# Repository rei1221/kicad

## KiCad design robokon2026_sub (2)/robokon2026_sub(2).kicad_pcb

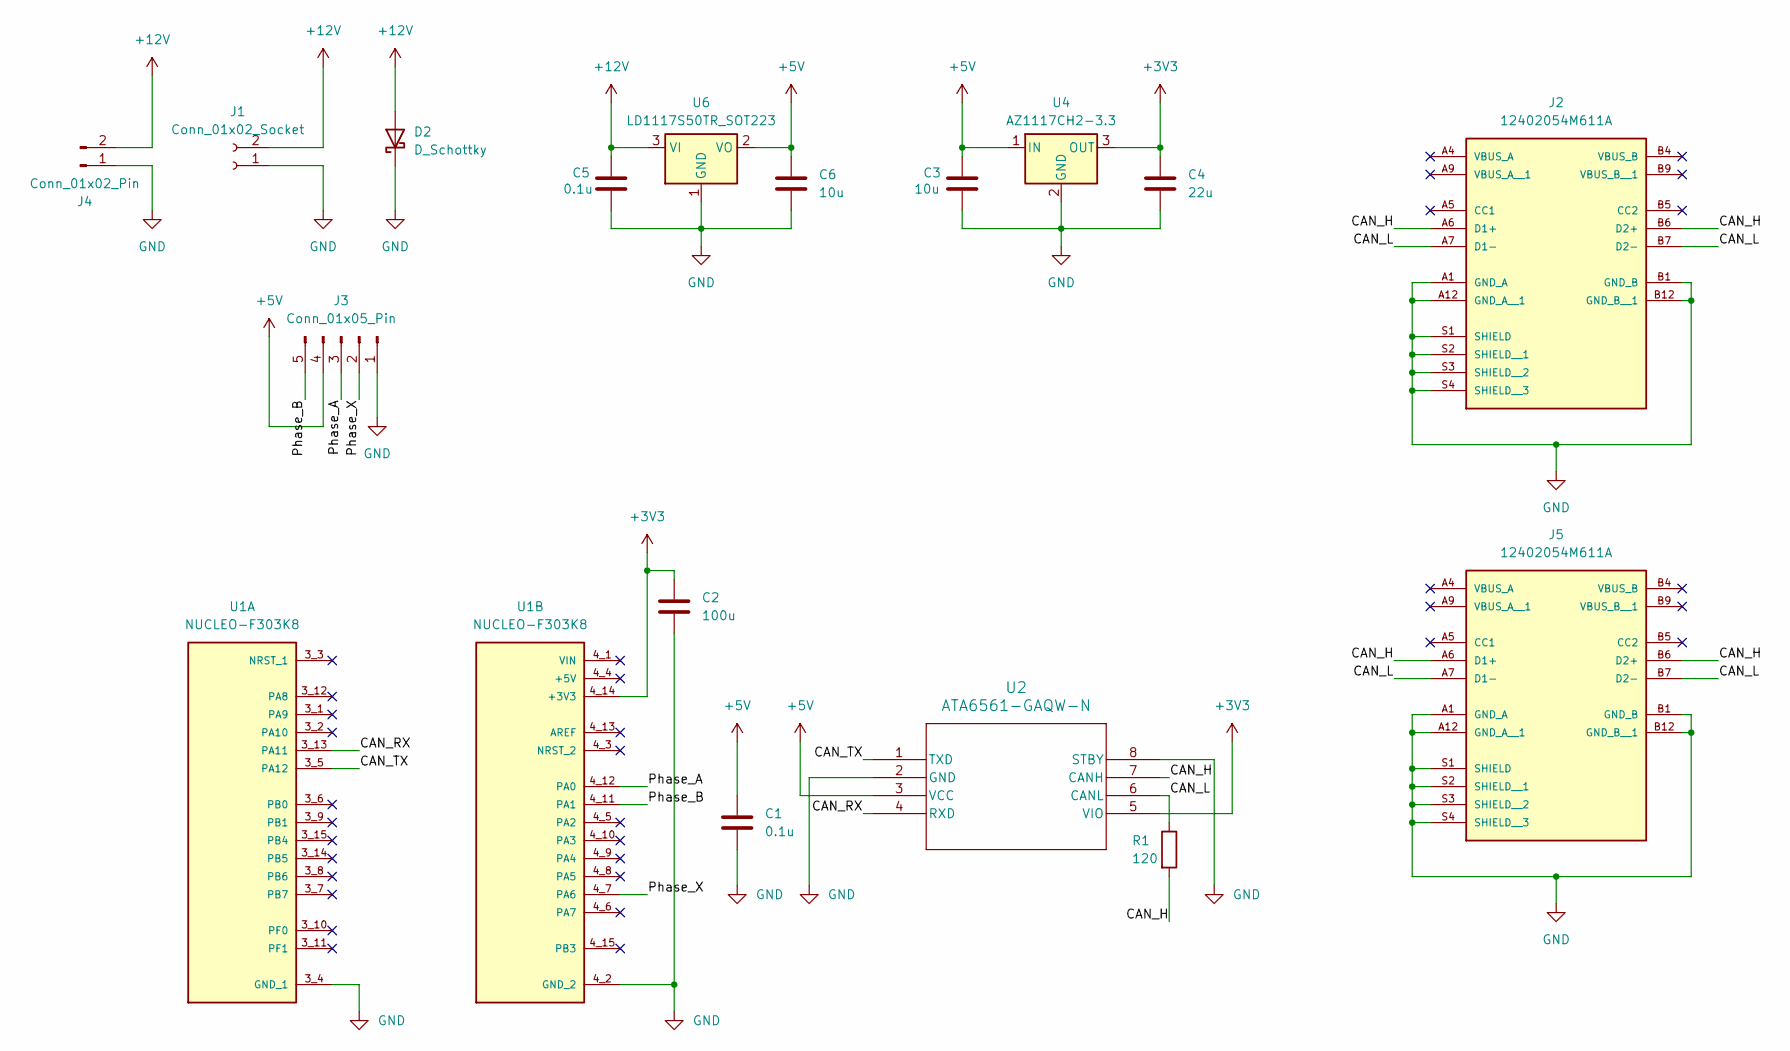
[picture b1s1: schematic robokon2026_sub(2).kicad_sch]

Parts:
C1, C5: 0.1u; C_0805_2012Metric_Pad1.18x1.45mm_HandSolder
C2: 100u; CP_Radial_D10.0mm_P5.00mm
C3, C6: 10u; C_0805_2012Metric_Pad1.18x1.45mm_HandSolder
C4: 22u; C_0805_2012Metric_Pad1.18x1.45mm_HandSolder
D2: D_Schottky; D_SMC
J1: Conn_01x02_Socket; AMASS_XT30PW-F_1x02_P2.50mm_Horizontal
J2, J5: 12402054M611A; AMPHENOL_12402054M611A; PARTREV 3
J3: Conn_01x05_Pin; JST_XH_S5B-XH-A_1x05_P2.50mm_Horizontal
J4: Conn_01x02_Pin; AMASS_XT30PW-M_1x02_P2.50mm_Horizontal
R1: 120; R_0603_1608Metric_Pad0.98x0.95mm_HandSolder
U1: NUCLEO-F303K8; MODULE_NUCLEO-F303K8; PARTREV 5; DigiKey_Part_Number 497-15981-ND
U2: ATA6561-GAQW-N; SOIC8_4P9X3P9MC_MCH
U4: AZ1117CH2-3.3; SOT-223-3_TabPin2
U6: LD1117S50TR_SOT223; SOT-223-3_TabPin2

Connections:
+3V3: C2.1, C4.1, U1.4_14 (+3V3), U2.5 (VIO), U4.3 (OUT)
+5V: C1.1, C3.1, C6.1, J3.4, U2.3 (VCC), U4.1 (IN), U6.2 (VO)
+12V: C5.1, D2.2 (A), J1.2, J4.2, U6.3 (VI)
/CAN_H: J2.A6 (D1+), J2.B6 (D2+), J5.A6 (D1+), J5.B6 (D2+), R1.2, U2.7 (CANH)
/CAN_L: J2.A7 (D1-), J2.B7 (D2-), J5.A7 (D1-), J5.B7 (D2-), R1.1, U2.6 (CANL)
/CAN_RX: U1.3_13 (PA11), U2.4 (RXD)
/CAN_TX: U1.3_5 (PA12), U2.1 (TXD)
/Phase_A: J3.3, U1.4_12 (PA0)
/Phase_B: J3.5, U1.4_11 (PA1)
/Phase_X: J3.2, U1.4_7 (PA6)
GND: C1.2, C2.2, C3.2, C4.2, C5.2, C6.2, D2.1 (K), J1.1, J2.A1 (GND_A), J2.A12 (GND_A__1), J2.B1 (GND_B), J2.B12 (GND_B__1), J2.S1 (SHIELD), J2.S2 (SHIELD__1), J2.S3 (SHIELD__2), J2.S4 (SHIELD__3), J3.1, J4.1, J5.A1 (GND_A), J5.A12 (GND_A__1), J5.B1 (GND_B), J5.B12 (GND_B__1), J5.S1 (SHIELD), J5.S2 (SHIELD__1), J5.S3 (SHIELD__2), J5.S4 (SHIELD__3), U1.3_4 (GND_1), U1.4_2 (GND_2), U2.2 (GND), U2.8 (STBY), U4.2 (GND), U6.1 (GND)

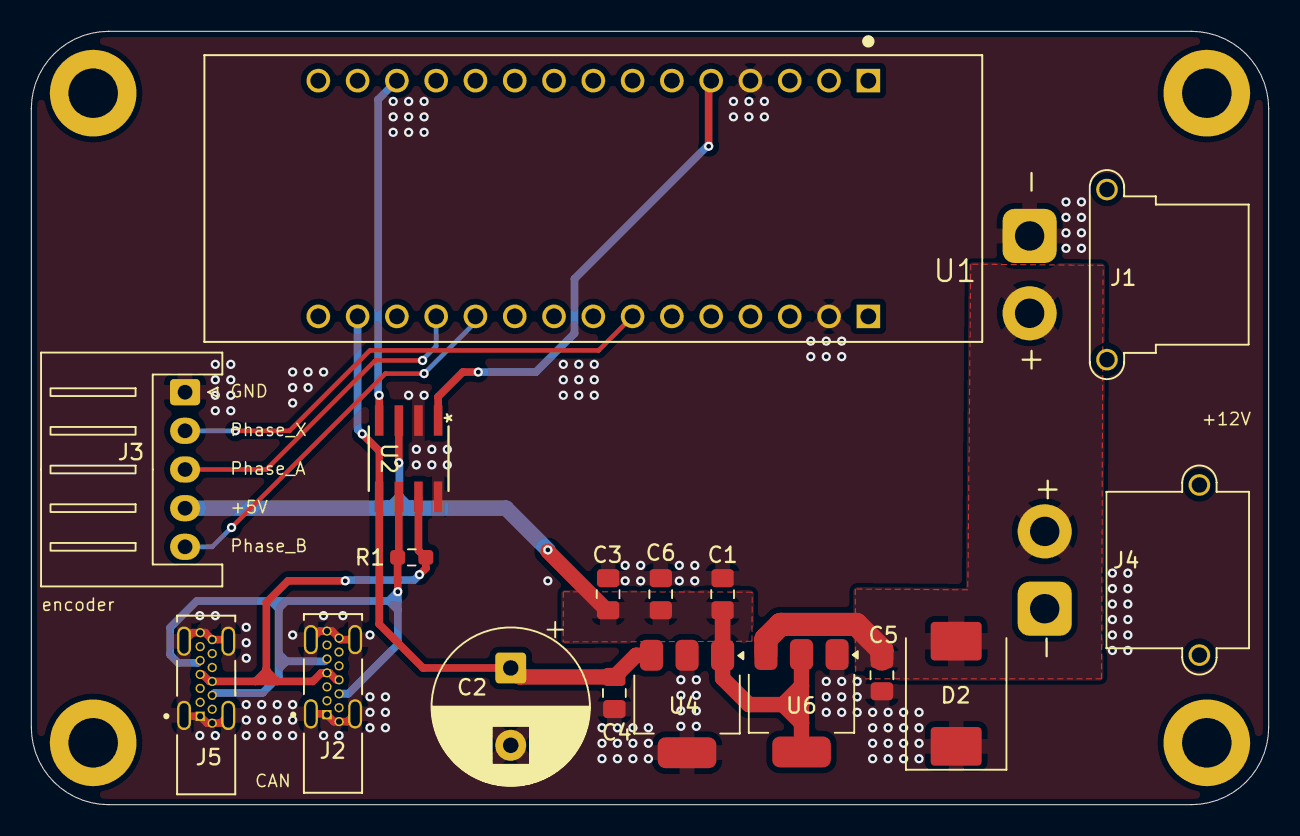
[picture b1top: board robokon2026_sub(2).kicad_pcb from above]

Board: 2 copper layers, 80.0 x 50.0 mm, 17 parts (0 on the bottom side), 11 nets.

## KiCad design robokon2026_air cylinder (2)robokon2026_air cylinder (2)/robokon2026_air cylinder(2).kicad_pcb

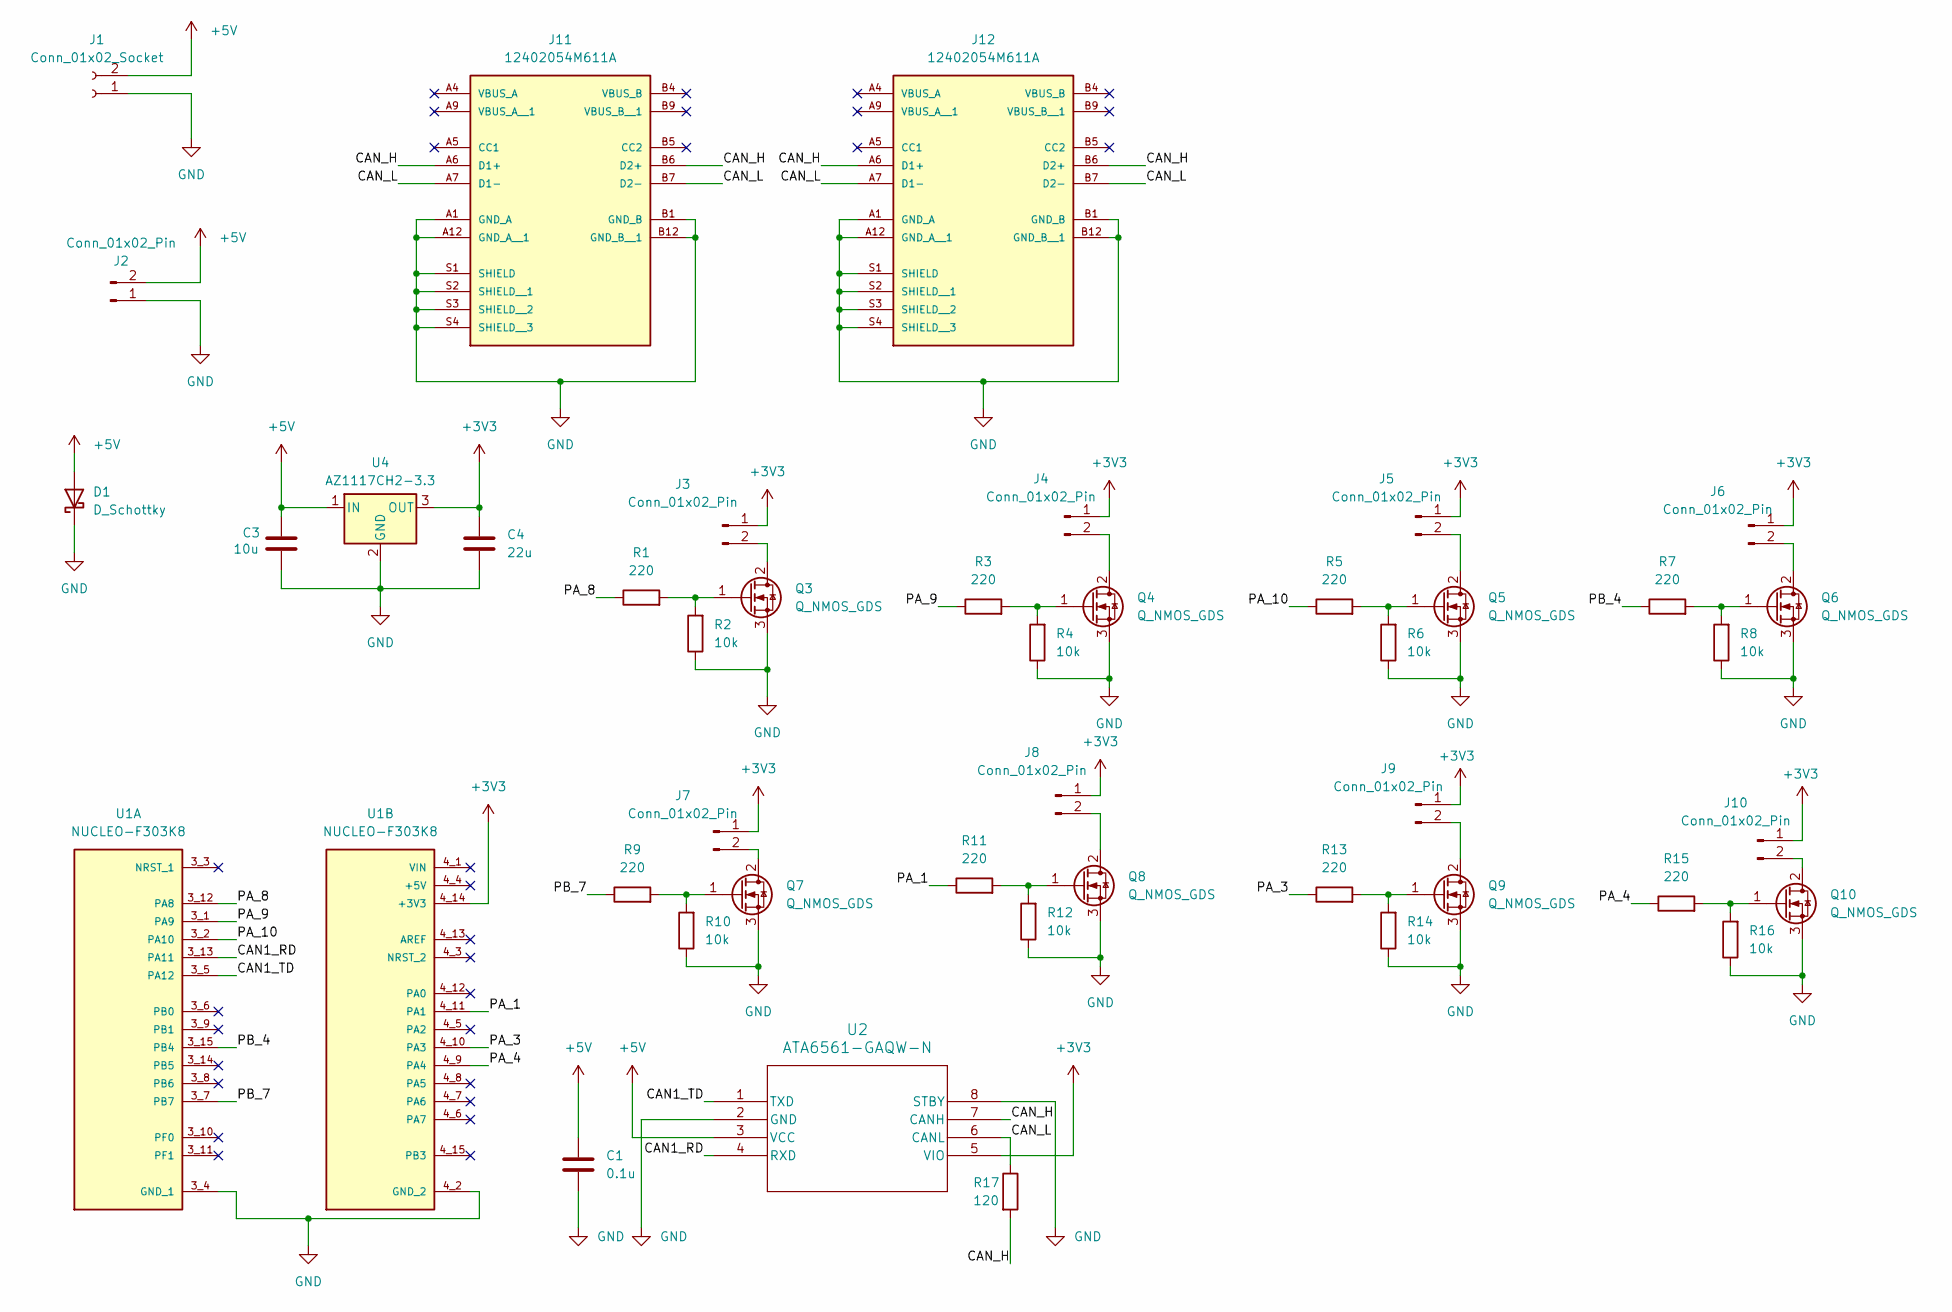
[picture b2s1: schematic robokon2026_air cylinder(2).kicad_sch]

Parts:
C1: 0.1u; C_0805_2012Metric_Pad1.18x1.45mm_HandSolder
C3: 10u; C_0805_2012Metric_Pad1.18x1.45mm_HandSolder
C4: 22u; C_0805_2012Metric_Pad1.18x1.45mm_HandSolder
D1: D_Schottky; D_SMC
J1: Conn_01x02_Socket; AMASS_XT30PW-F_1x02_P2.50mm_Horizontal
J2: Conn_01x02_Pin; AMASS_XT30PW-M_1x02_P2.50mm_Horizontal
J3, J4, J5, J6, J7, J8, J9, J10: Conn_01x02_Pin; CONN_B02B-PASKLFSN_JST
J11, J12: 12402054M611A; AMPHENOL_12402054M611A; PARTREV 3
Q3, Q4, Q5, Q6, Q7, Q8, Q9, Q10: Q_NMOS_GDS; TO-252-3_TabPin2
R1, R3, R5, R7, R9, R11, R13, R15: 220; R_0603_1608Metric_Pad0.98x0.95mm_HandSolder
R2, R4, R6, R8, R10, R12, R14, R16: 10k; R_0603_1608Metric_Pad0.98x0.95mm_HandSolder
R17: 120; R_0603_1608Metric_Pad0.98x0.95mm_HandSolder
U1: NUCLEO-F303K8; MODULE_NUCLEO-F303K8; PARTREV 5; DigiKey_Part_Number 497-15981-ND
U2: ATA6561-GAQW-N; SOIC8_4P9X3P9MC_MCH
U4: AZ1117CH2-3.3; SOT-223-3_TabPin2

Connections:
+3V3: C4.1, J3.1, J4.1, J5.1, J6.1, J7.1, J8.1, J9.1, J10.1, U1.4_14 (+3V3), U2.5 (VIO), U4.3 (OUT)
+5V: C1.1, C3.1, D1.2 (A), J1.2, J2.2, U2.3 (VCC), U4.1 (IN)
/CAN1_RD: U1.3_13 (PA11), U2.4 (RXD)
/CAN1_TD: U1.3_5 (PA12), U2.1 (TXD)
/CAN_H: J11.A6 (D1+), J11.B6 (D2+), J12.A6 (D1+), J12.B6 (D2+), R17.2, U2.7 (CANH)
/CAN_L: J11.A7 (D1-), J11.B7 (D2-), J12.A7 (D1-), J12.B7 (D2-), R17.1, U2.6 (CANL)
/PA_1: R11.1, U1.4_11 (PA1)
/PA_3: R13.1, U1.4_10 (PA3)
/PA_4: R15.1, U1.4_9 (PA4)
/PA_8: R1.1, U1.3_12 (PA8)
/PA_9: R3.1, U1.3_1 (PA9)
/PA_10: R5.1, U1.3_2 (PA10)
/PB_4: R7.1, U1.3_15 (PB4)
/PB_7: R9.1, U1.3_7 (PB7)
GND: C1.2, C3.2, C4.2, D1.1 (K), J1.1, J2.1, J11.A1 (GND_A), J11.A12 (GND_A__1), J11.B1 (GND_B), J11.B12 (GND_B__1), J11.S1 (SHIELD), J11.S2 (SHIELD__1), J11.S3 (SHIELD__2), J11.S4 (SHIELD__3), J12.A1 (GND_A), J12.A12 (GND_A__1), J12.B1 (GND_B), J12.B12 (GND_B__1), J12.S1 (SHIELD), J12.S2 (SHIELD__1), J12.S3 (SHIELD__2), J12.S4 (SHIELD__3), Q3.3 (S), Q4.3 (S), Q5.3 (S), Q6.3 (S), Q7.3 (S), Q8.3 (S), Q9.3 (S), Q10.3 (S), R2.1, R4.1, R6.1, R8.1, R10.1, R12.1, R14.1, R16.1, U1.3_4 (GND_1), U1.4_2 (GND_2), U2.2 (GND), U2.8 (STBY), U4.2 (GND)
unnamed: J3.2, Q3.2 (D)
unnamed: J4.2, Q4.2 (D)
unnamed: J5.2, Q5.2 (D)
unnamed: J6.2, Q6.2 (D)
unnamed: J7.2, Q7.2 (D)
unnamed: J8.2, Q8.2 (D)
unnamed: J9.2, Q9.2 (D)
unnamed: J10.2, Q10.2 (D)
unnamed: Q3.1 (G), R1.2, R2.2
unnamed: Q4.1 (G), R3.2, R4.2
unnamed: Q5.1 (G), R5.2, R6.2
unnamed: Q6.1 (G), R7.2, R8.2
unnamed: Q7.1 (G), R9.2, R10.2
unnamed: Q8.1 (G), R11.2, R12.2
unnamed: Q9.1 (G), R13.2, R14.2
unnamed: Q10.1 (G), R15.2, R16.2

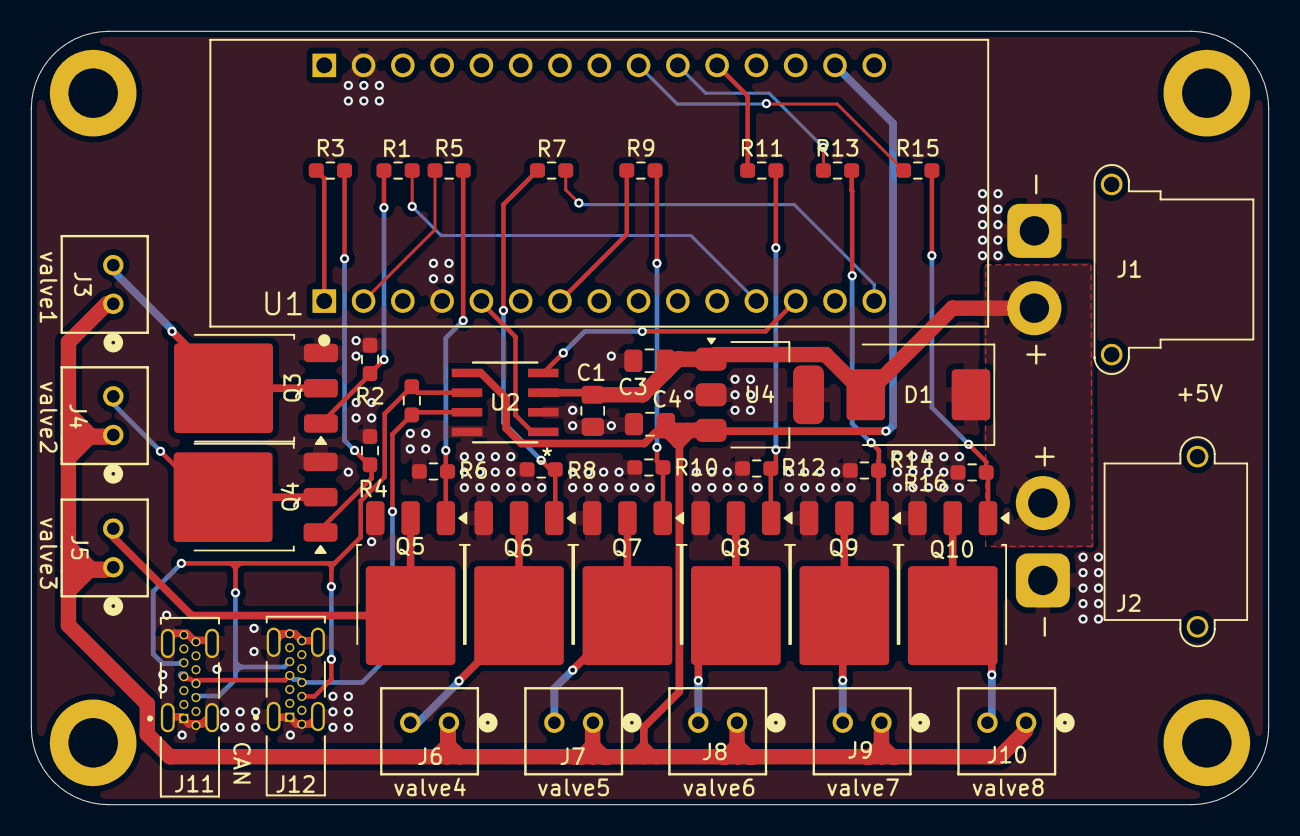
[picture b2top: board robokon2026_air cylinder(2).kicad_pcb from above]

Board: 2 copper layers, 80.0 x 50.0 mm, 44 parts (0 on the bottom side), 31 nets.

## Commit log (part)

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2026-04-24 Add robokon2026_sub
2026-04-26 add robokon2026_sub/pcb
2026-04-28 improvement1/robokon2026_sub
2026-05-01 improvement2/robokon2026_sub
2026-06-16 Create 1
2026-06-16 Create robokon2026_air cylinder (2)
